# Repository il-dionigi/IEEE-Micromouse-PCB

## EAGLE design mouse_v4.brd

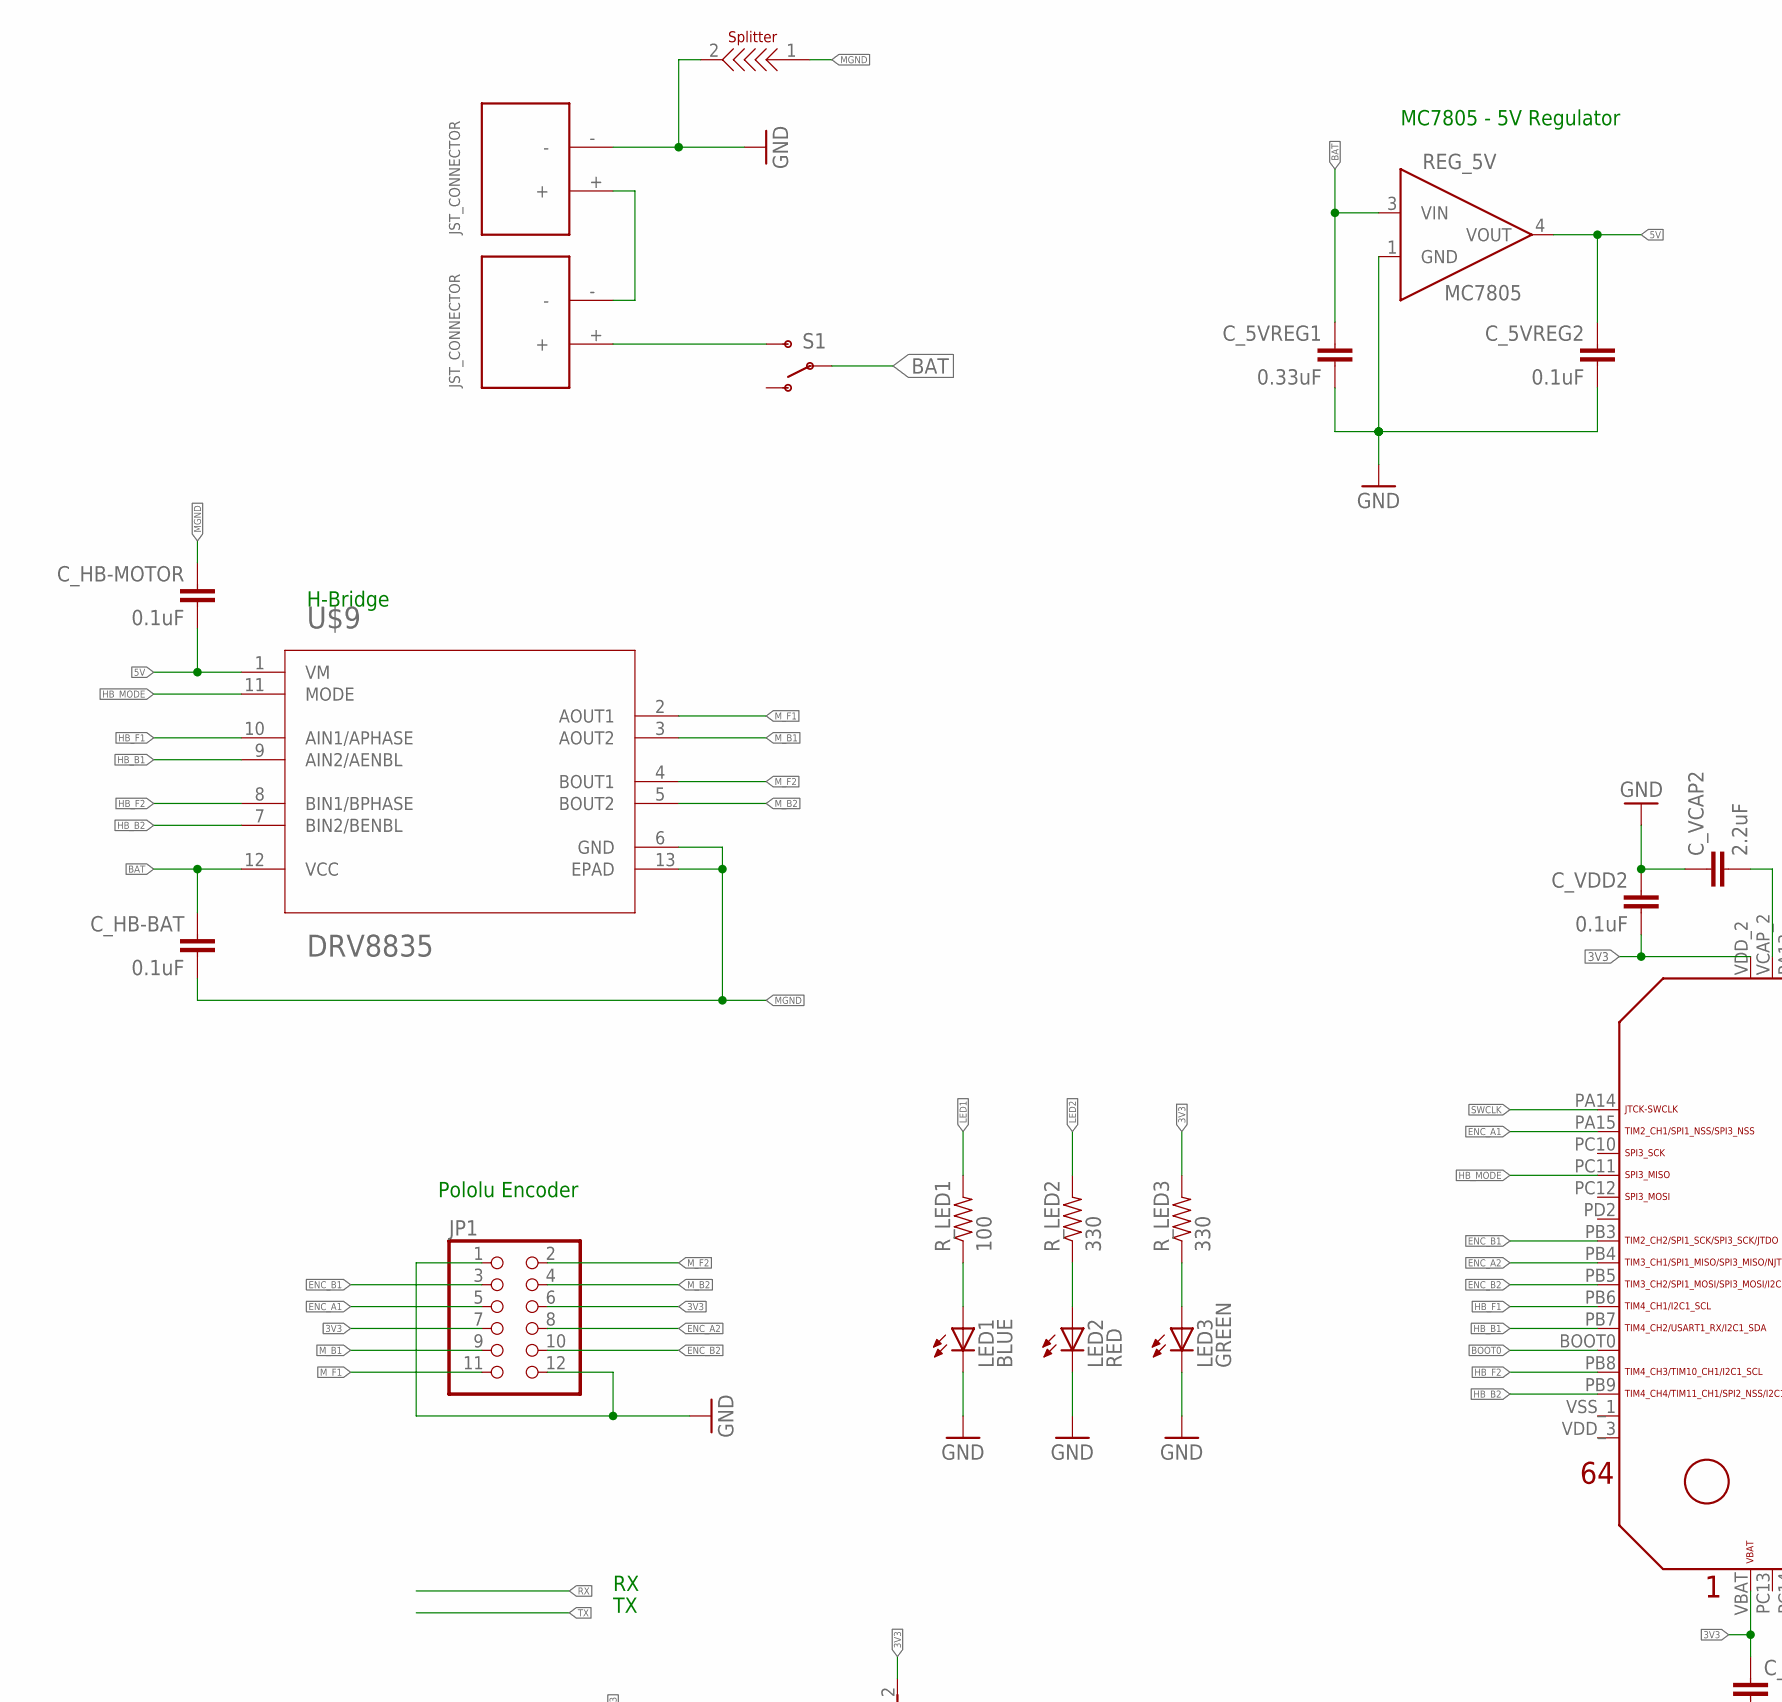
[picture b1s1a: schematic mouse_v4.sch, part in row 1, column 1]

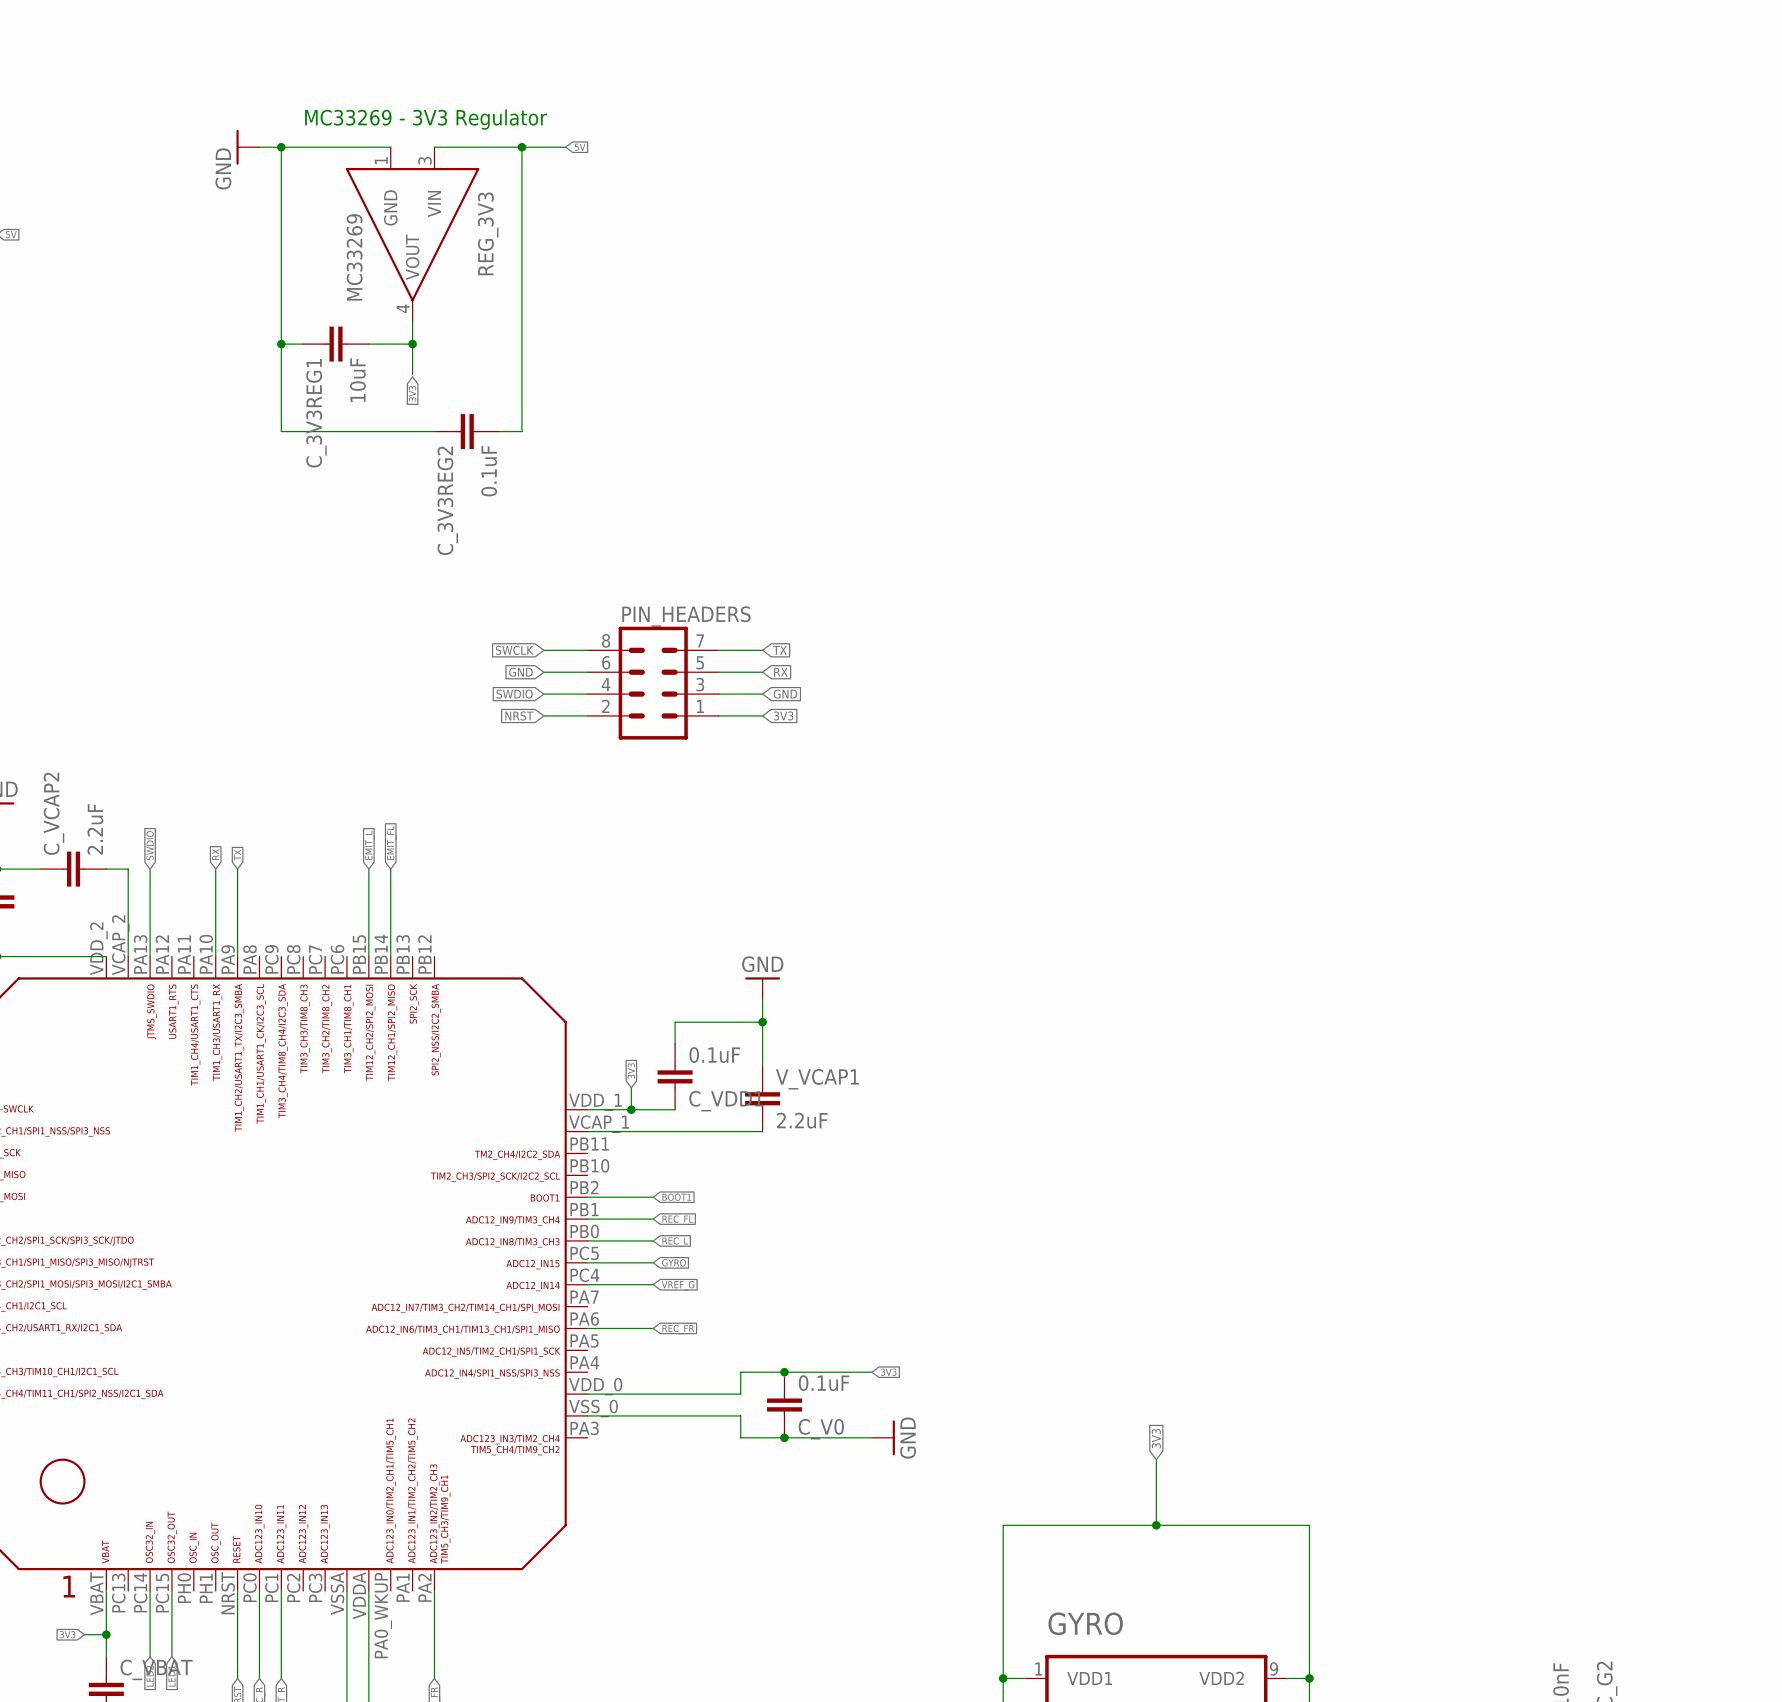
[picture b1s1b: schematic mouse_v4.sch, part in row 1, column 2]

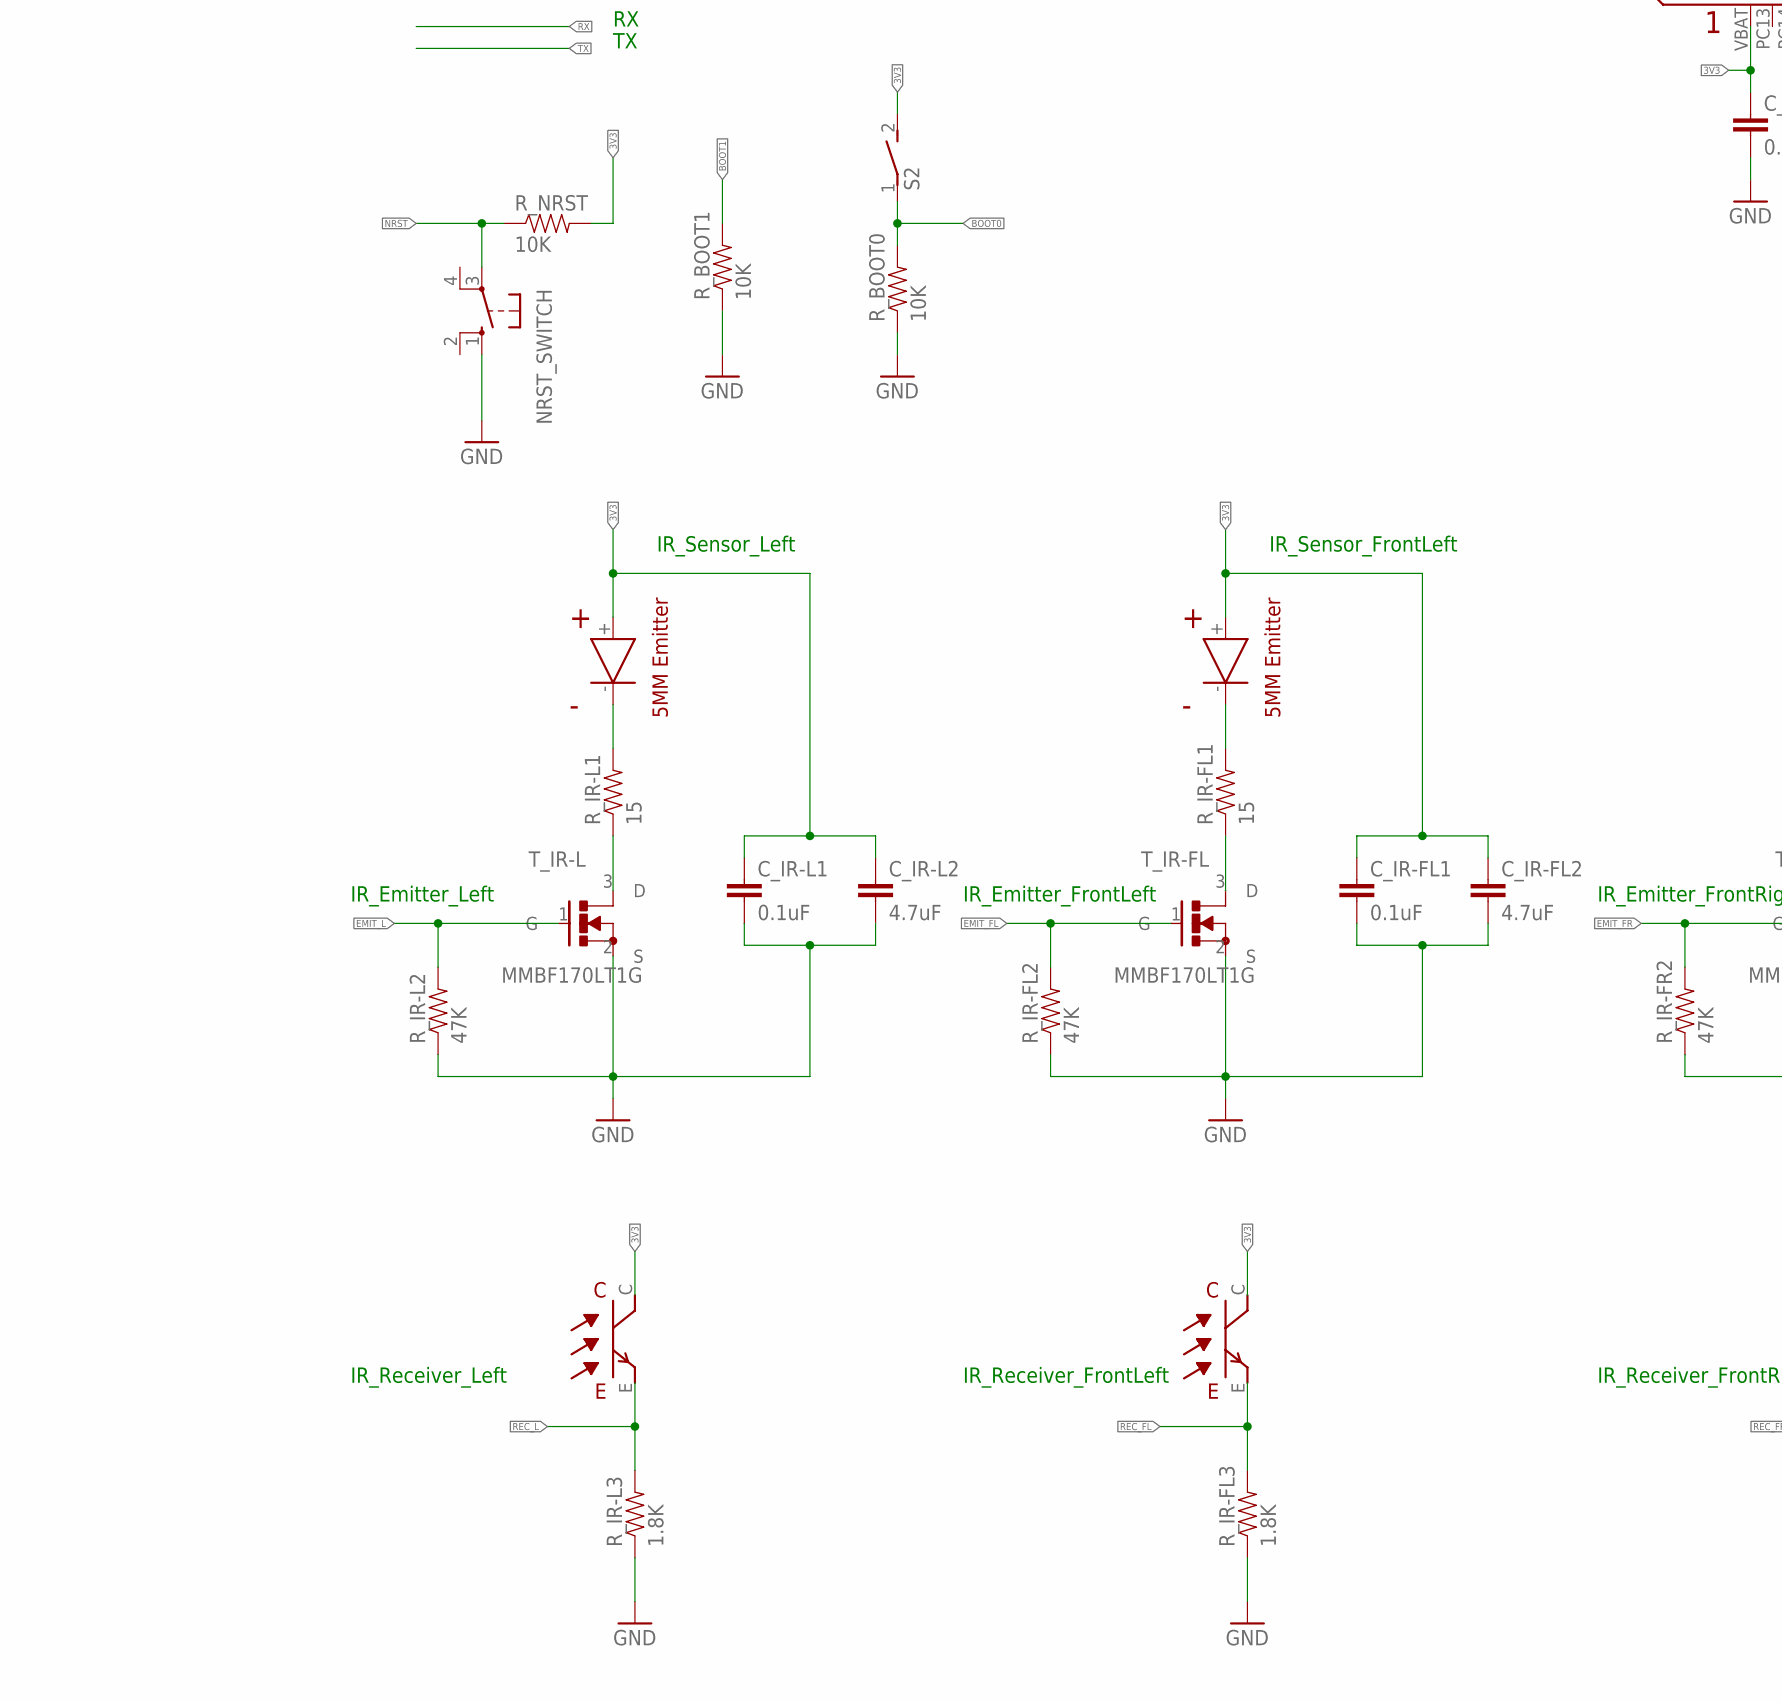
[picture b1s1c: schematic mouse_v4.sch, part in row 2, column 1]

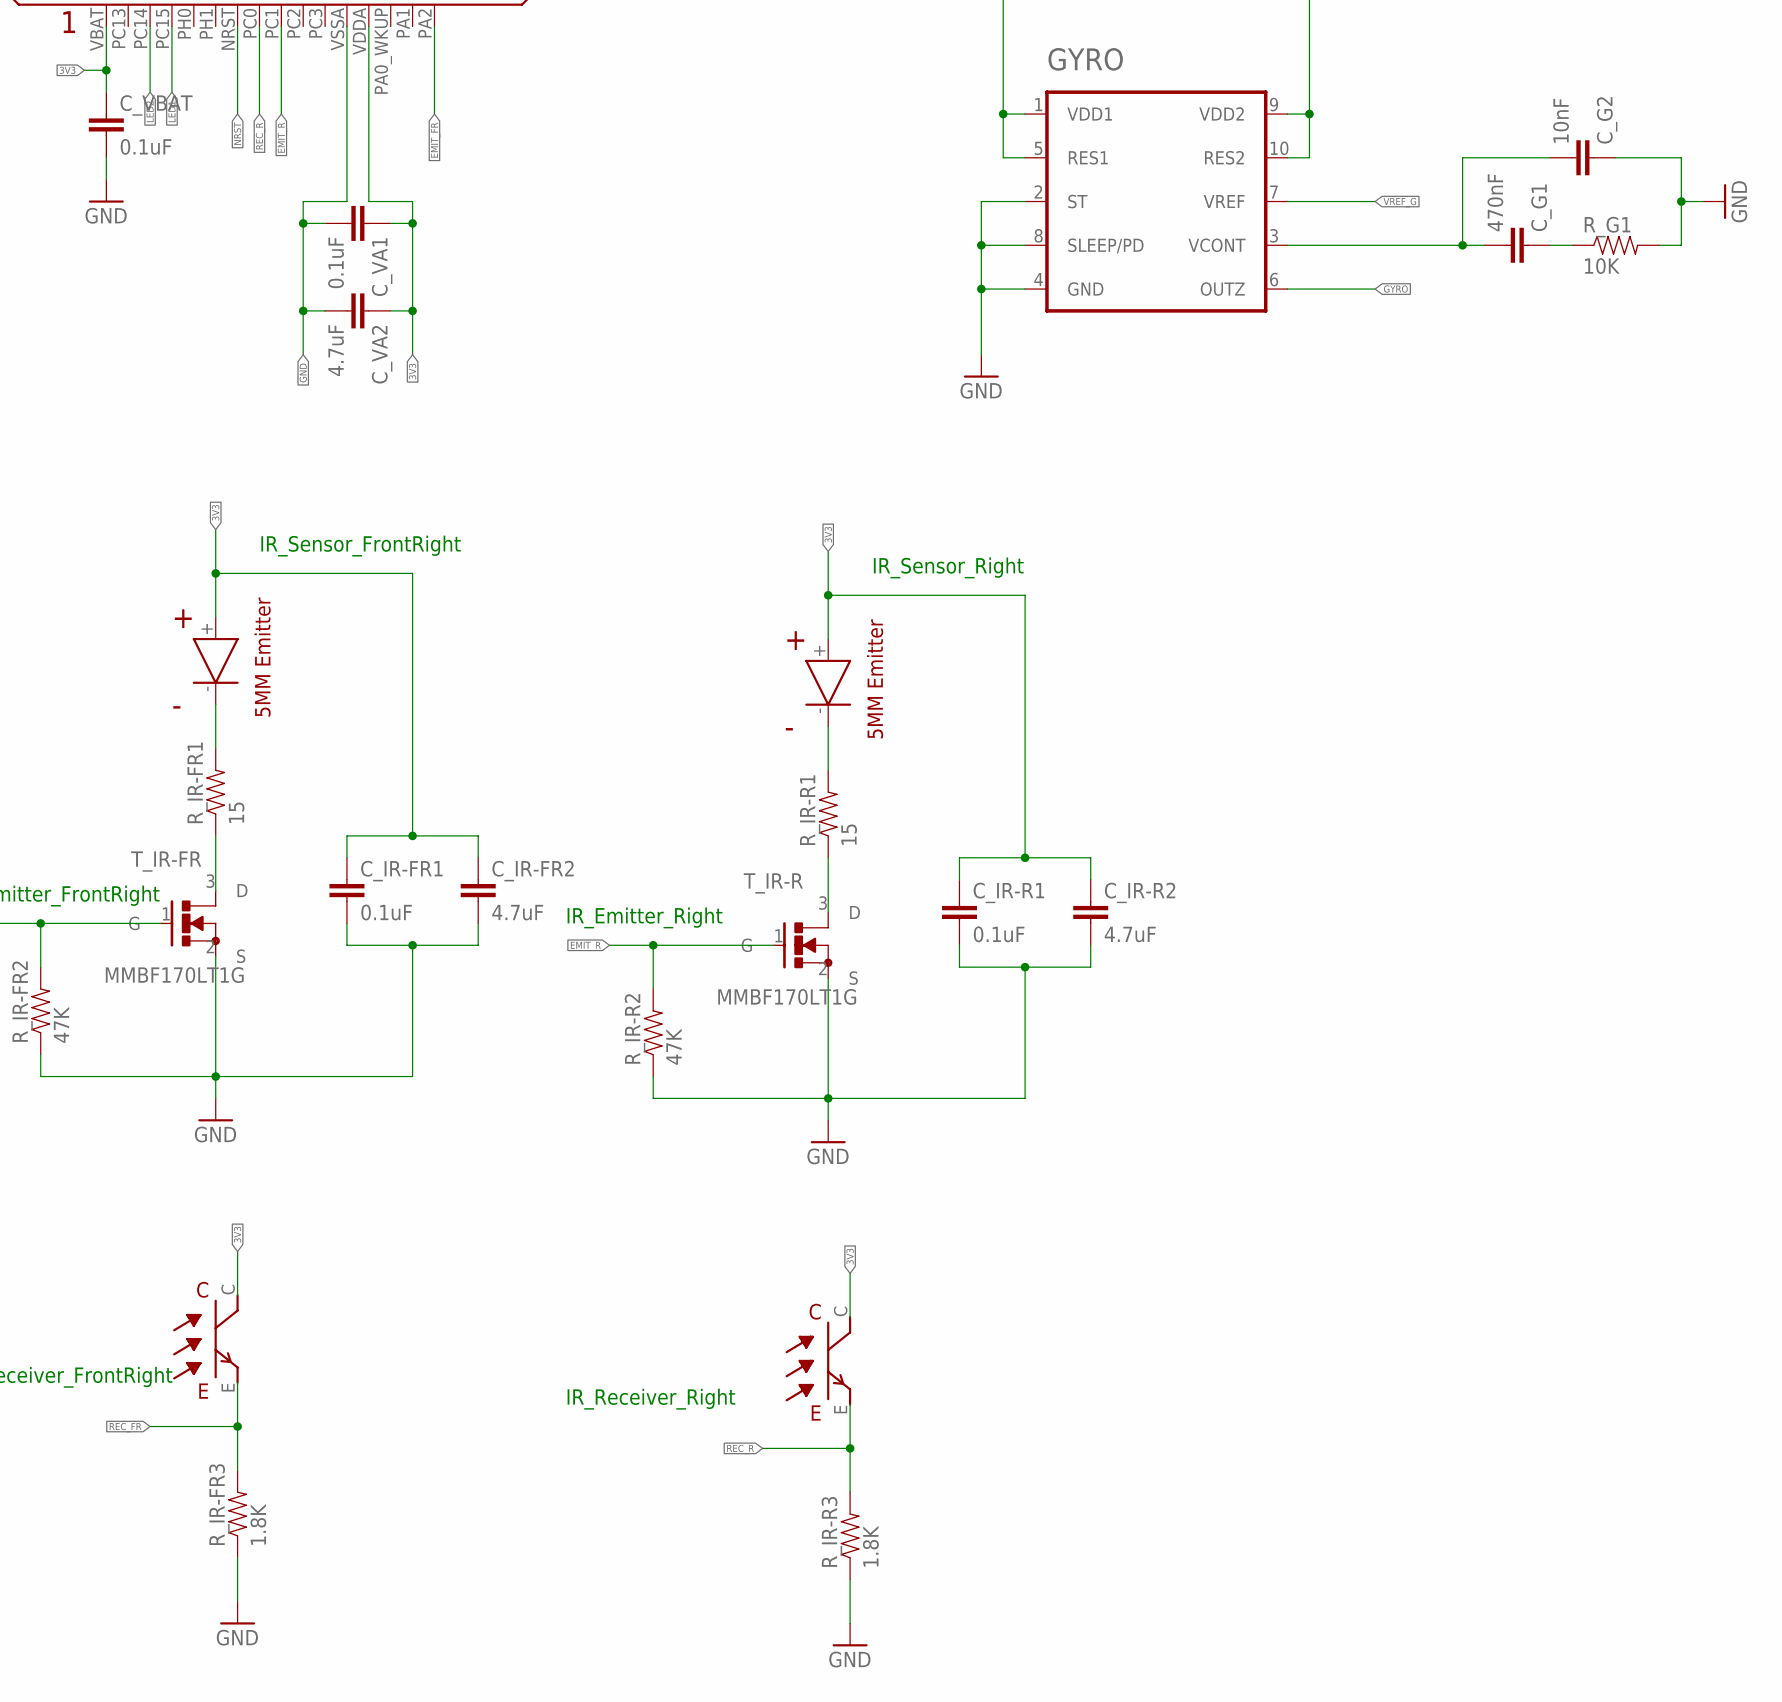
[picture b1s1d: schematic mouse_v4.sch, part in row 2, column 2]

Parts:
C_3V3REG1: 10uF; 0603-CAP
C_3V3REG2, C_5VREG2: 0.1uF; 0603-CAP
C_5VREG1: 0.33uF; 0603-CAP
C_G1: 470nF; 0603-CAP
C_G2: 10nF; 0603-CAP
C_HB-BAT: 0.1uF; 0603-CAP
C_HB-MOTOR: 0.1uF; 0603-CAP
C_IR-FL1: 0.1uF; 0603-CAP
C_IR-FL2: 4.7uF; 0603-CAP
C_IR-FR1: 0.1uF; 0603-CAP
C_IR-FR2: 4.7uF; 0603-CAP
C_IR-L1: 0.1uF; 0603-CAP
C_IR-L2: 4.7uF; 0603-CAP
C_IR-R1: 0.1uF; 0603-CAP
C_IR-R2: 4.7uF; 0603-CAP
C_V0: 0.1uF; 0603-CAP
C_VA1: 0.1uF; 0603-CAP
C_VA2: 4.7uF; 0603-CAP
C_VBAT: 0.1uF; 0603-CAP
C_VCAP2: 2.2uF; 0603-CAP
C_VDD1, C_VDD2: 0.1uF; 0603-CAP
GYRO: LY3200ALH; 10-TLGA
IR_FL: EMITTER
IR_FR: EMITTER
IR_L: EMITTER
IR_R: EMITTER
JP1: PINHD-2X6; 2X06
LED1: BLUE; CHIPLED_0603
LED2: RED; CHIPLED_0603
LED3: GREEN; CHIPLED_0603
NRST_SWITCH: 10-XX; B3F-10XX
PIN_HEADERS: MA04-2
REG_3V3: MC33269; TO-252-3
REG_5V: MC7805; TO-252-3
R_BOOT0, R_BOOT1: 10K; 0603-RES
R_G1: 10K; 0603-RES
R_IR-FL1: 15; 0603-RES
R_IR-FL2: 47K; 0603-RES
R_IR-FL3: 1.8K; 0603-RES
R_IR-FR1: 15; 0603-RES
R_IR-FR2: 47K; 0603-RES
R_IR-FR3: 1.8K; 0603-RES
R_IR-L1: 15; 0603-RES
R_IR-L2: 47K; 0603-RES
R_IR-L3: 1.8K; 0603-RES
R_IR-R1: 15; 0603-RES
R_IR-R2: 47K; 0603-RES
R_IR-R3: 1.8K; 0603-RES
R_LED1: 100; 0603-RES
R_LED2, R_LED3: 330; 0603-RES
R_NRST: 10K; 0603-RES
S1: SWITCH-SPSTKIT; SWITCH-SPDT_KIT
S2: DS01E; DS-01
T_IR-FL: MMBF170LT1G; SOT-23
T_IR-FR: MMBF170LT1G; SOT-23
T_IR-L: MMBF170LT1G; SOT-23
T_IR-R: MMBF170LT1G; SOT-23
U$1: STM32F405/415_LQFP64
U$2, U$3: JST_CONNECTOR_FEMALE
U$4, U$5, U$6, U$7: RECEIVER
U$8: SPLITTER
U$9: DRV8835; 12-WFDFN
V_VCAP1: 2.2uF; 0603-CAP

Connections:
3V3: C_3V3REG1.2, C_IR-FL1.1, C_IR-FL2.1, C_IR-FR1.1, C_IR-FR2.1, C_IR-L1.1, C_IR-L2.1, C_IR-R1.1, C_IR-R2.1, C_V0.2, C_VA1.1, C_VA2.1, C_VBAT.1, C_VDD1.1, C_VDD2.2, GYRO.1 (VDD1), GYRO.5 (RES1), GYRO.9 (VDD2), GYRO.10 (RES2), IR_FL.+, IR_FR.+, IR_L.+, IR_R.+, JP1.6, JP1.7, PIN_HEADERS.1, REG_3V3.4 (VOUT), R_LED3.2, R_NRST.2, S2.2, U$1.VBAT, U$1.VDDA, U$1.VDD_0, U$1.VDD_1, U$1.VDD_2, U$4.C, U$5.C, U$6.C, U$7.C
5V: C_3V3REG2.2, C_5VREG2.1, C_HB-MOTOR.2, REG_3V3.3 (VIN), REG_5V.4 (VOUT), U$9.1 (VM)
BAT: C_5VREG1.1, C_HB-BAT.1, REG_5V.3 (VIN), S1.2, U$9.12 (VCC)
BOOT0: R_BOOT0.2, S2.1, U$1.BOOT0
BOOT1: R_BOOT1.2, U$1.PB2
EMIT_FL: R_IR-FL2.2, T_IR-FL.1 (G), U$1.PB14
EMIT_FR: R_IR-FR2.2, T_IR-FR.1 (G), U$1.PA2
EMIT_L: R_IR-L2.2, T_IR-L.1 (G), U$1.PB15
EMIT_R: R_IR-R2.2, T_IR-R.1 (G), U$1.PC1
ENC_A1: JP1.5, U$1.PA15
ENC_A2: JP1.8, U$1.PB4
ENC_B1: JP1.3, U$1.PB3
ENC_B2: JP1.10, U$1.PB5
GND: C_3V3REG1.1, C_3V3REG2.1, C_5VREG1.2, C_5VREG2.2, C_G2.1, C_IR-FL1.2, C_IR-FL2.2, C_IR-FR1.2, C_IR-FR2.2, C_IR-L1.2, C_IR-L2.2, C_IR-R1.2, C_IR-R2.2, C_V0.1, C_VA1.2, C_VA2.2, C_VBAT.2, C_VCAP2.1, C_VDD1.2, C_VDD2.1, GYRO.2 (ST), GYRO.4 (GND), GYRO.8 (SLEEP/PD), JP1.1, JP1.12, LED1.C, LED2.C, LED3.C, NRST_SWITCH.1 (S), PIN_HEADERS.3, PIN_HEADERS.6, REG_3V3.1 (GND), REG_5V.1 (GND), R_BOOT0.1, R_BOOT1.1, R_G1.2, R_IR-FL2.1, R_IR-FL3.1, R_IR-FR2.1, R_IR-FR3.1, R_IR-L2.1, R_IR-L3.1, R_IR-R2.1, R_IR-R3.1, T_IR-FL.2 (S), T_IR-FR.2 (S), T_IR-L.2 (S), T_IR-R.2 (S), U$1.VSSA, U$1.VSS_0, U$2.-, U$8.2, V_VCAP1.1
GYRO: GYRO.6 (OUTZ), U$1.PC5
HB_B1: U$1.PB7, U$9.9 (AIN2/AENBL)
HB_B2: U$1.PB9, U$9.7 (BIN2/BENBL)
HB_F1: U$1.PB6, U$9.10 (AIN1/APHASE)
HB_F2: U$1.PB8, U$9.8 (BIN1/BPHASE)
HB_MODE: U$1.PC11, U$9.11 (MODE)
LED1: R_LED1.2, U$1.PC15
LED2: R_LED2.2, U$1.PC14
MGND: C_HB-BAT.2, C_HB-MOTOR.1, U$8.1, U$9.6 (GND), U$9.13 (EPAD)
M_B1: JP1.9, U$9.3 (AOUT2)
M_B2: JP1.4, U$9.5 (BOUT2)
M_F1: JP1.11, U$9.2 (AOUT1)
M_F2: JP1.2, U$9.4 (BOUT1)
unnamed: C_VCAP2.2, U$1.VCAP_2
unnamed: U$2.+, U$3.-
unnamed: U$1.VCAP_1, V_VCAP1.2
unnamed: C_G1.1, R_G1.1
unnamed: S1.3 (S), U$3.+
unnamed: IR_FR.-, R_IR-FR1.2
unnamed: LED1.A, R_LED1.1
unnamed: C_G1.2, C_G2.2, GYRO.3 (VCONT)
unnamed: LED2.A, R_LED2.1
unnamed: LED3.A, R_LED3.1
unnamed: R_IR-FR1.1, T_IR-FR.3 (D)
unnamed: IR_R.-, R_IR-R1.2
unnamed: IR_FL.-, R_IR-FL1.2
unnamed: R_IR-FL1.1, T_IR-FL.3 (D)
unnamed: R_IR-R1.1, T_IR-R.3 (D)
unnamed: IR_L.-, R_IR-L1.2
unnamed: R_IR-L1.1, T_IR-L.3 (D)
NRST: NRST_SWITCH.3, PIN_HEADERS.2, R_NRST.1, U$1.NRST
REC_FL: R_IR-FL3.2, U$1.PB1, U$5.E
REC_FR: R_IR-FR3.2, U$1.PA6, U$6.E
REC_L: R_IR-L3.2, U$1.PB0, U$4.E
REC_R: R_IR-R3.2, U$1.PC0, U$7.E
RX: PIN_HEADERS.5, U$1.PA10
SWCLK: PIN_HEADERS.8, U$1.PA14
SWDIO: PIN_HEADERS.4, U$1.PA13
TX: PIN_HEADERS.7, U$1.PA9
VREF_G: GYRO.7 (VREF), U$1.PC4

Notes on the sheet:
MC7805 - 5V Regulator
MC33269 - 3V3 Regulator
Pololu Encoder
IR_Sensor_FrontLeft
IR_Sensor_FrontRight
IR_Sensor_Right
IR_Sensor_Left
IR_Receiver_FrontLeft
IR_Receiver_FrontRight
IR_Receiver_Right
IR_Receiver_Left
IR_Emitter_Left
IR_Emitter_FrontLeft
IR_Emitter_FrontRight
IR_Emitter_Right
H-Bridge

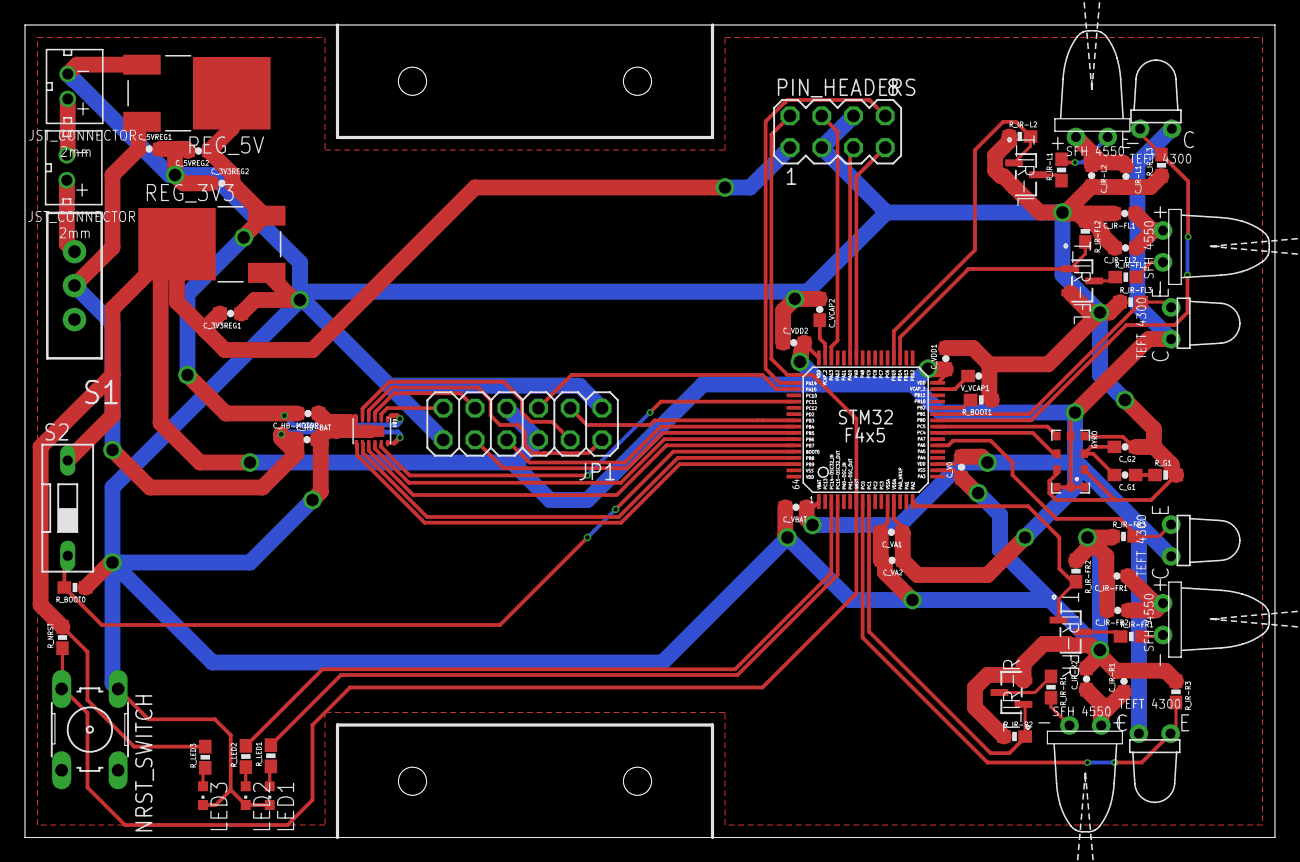
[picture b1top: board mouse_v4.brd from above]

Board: 2 copper layers, 100.0 x 65.0 mm, 71 parts (0 on the bottom side), 54 nets.

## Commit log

2018-12-21 LED Resistor
    1000 -> 100
2018-12-27 Throughput -> SMD MOSFET + REG
    Added SMD mosfet and regulator libraries, and added them to the schematic in place of the old throughput parts
2018-12-27 Added BOOT and NRST
2018-12-28 Created Gyro package
    Created gyro (LY3200ALH) library and added it to the schematic. Not wired.
2018-12-28 Added Gyro and Pin headers
2018-12-28 More LEDs
    Added green and red LED for debugging. Red is programmable, green tells if mouse is powered.
2018-12-28 ENC_B2 pin change
    Changed from PC4 -> PA3. PC4 is an ADC pin while we need a PWM (TIM) pin for the encoders.
2018-12-30 Schematic v2
    Take 2
2019-01-03 Switched out H-bridge
    Switched H-bridge for one with a higher max current
2019-01-03 cleaned files
    Rid of s#_ files and renamed v2 to c3
2019-01-10 pinout info
2019-01-12 v4 pre-polygon
    Moved H-Bridge closer
2019-01-13 Changed H-Bridge + Holes
    Changed the H-bridge smd layout and added holes for the wheel mounts
2019-01-15 polygon attempt pt2
    Removed all the small polygons and added a huge GND polygon on the bototm. Unsure what to do for the power polygons on top
2019-01-15 Changed IR LED Resistors
    Switched voltage from 5V to 3.3V for IR LEDs, and changed resistor values accordingly
2019-01-15 Added power plane
2019-01-22 updates I never pushed
2019-01-22 pcb width

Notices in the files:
parts and their libraries:
SparkFun: Licensing: CC v3.0 Share-Alike You are welcome to use this library for commercial purposes.
SparkFun-Resistors: Licensing: Creative Commons ShareAlike 4.0 International - https://creativecommons.org/licenses/by-sa/4.0
